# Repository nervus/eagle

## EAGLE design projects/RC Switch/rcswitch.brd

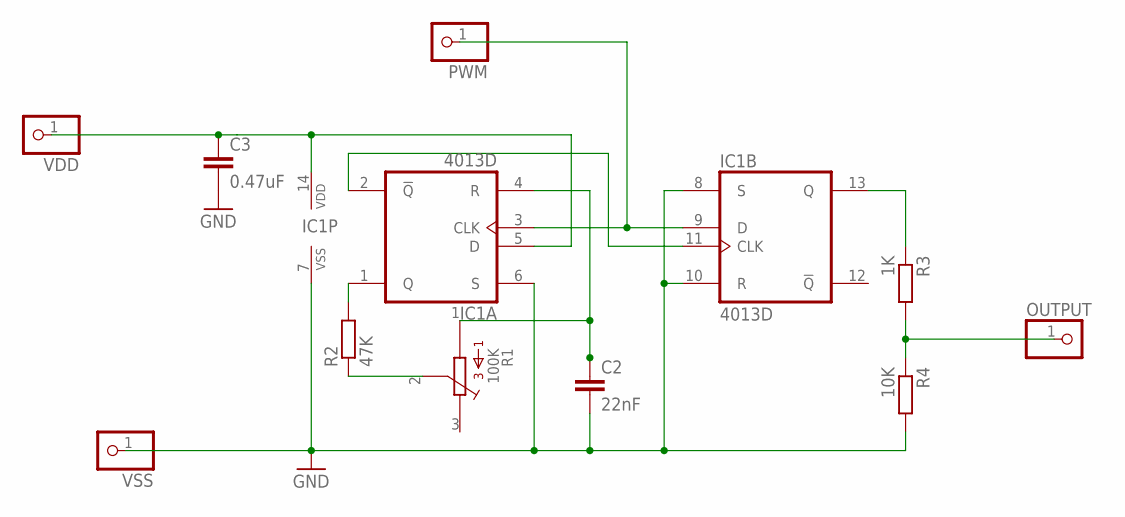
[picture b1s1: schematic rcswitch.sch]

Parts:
C2: 22nF; C3216
C3: 0.47uF; C3216
IC1: 4013D; SO14
OUTPUT: PINHD-1X1; 1X01
PWM: PINHD-1X1; 1X01
R1: 100K; 3386-MULTI
R2: 47K; R3225
R3: 1K; R3225
R4: 10K; R3225
VDD: PINHD-1X1; 1X01
VSS: PINHD-1X1; 1X01

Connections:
GND: C2.2, C3.2, IC1.6 (S), IC1.7 (VSS), IC1.8 (S), IC1.10 (R), R4.2, VSS.1
unnamed: IC1.1 (Q), R2.2
unnamed: R1.2, R2.1
unnamed: C2.1, IC1.4 (R), R1.1
unnamed: IC1.13 (Q), R3.1
unnamed: IC1.3 (CLK), IC1.9 (D), PWM.1
unnamed: IC1.2 (!Q), IC1.11 (CLK)
unnamed: C3.1, IC1.5 (D), IC1.14 (VDD), VDD.1
OUTPUT: OUTPUT.1, R3.2, R4.1

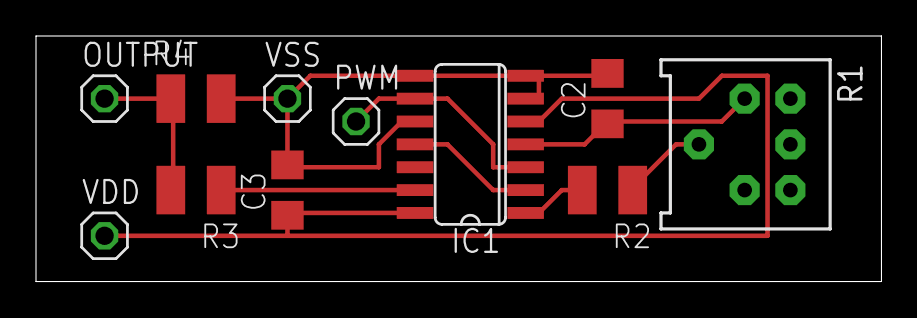
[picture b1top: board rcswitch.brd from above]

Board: 2 copper layers, 47.0 x 13.6 mm, 11 parts (0 on the bottom side), 9 nets.
